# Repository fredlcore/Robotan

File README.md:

# Robotan
Die deutsche Version gibt es <A HREF="README_de.md">hier</A>.  

WiFi access to Zucchetti-based lawnmower robots (Ambrogio, Stiga, Herkules etc.)  
See a list of (partly still assumed) compatible robots <A HREF="Supported Models.md">here</A>.  
Some boards left over from a collective order are still available. Contact robotan (ät) code-it.de if you are interested (German or English).

<H2><A HREF="LICENSE.md">License</A></H2>
<H2><A HREF="Assembly Instructions.md">Building the Robotan board</A></H2>
<H2><A HREF="Installation.md">Installation</A></H2>
<H2><A HREF="Setup.md">Software Setup</A></H2>
<H2><A HREF="Configuration.md">Configuration</A></H2>
<H2><A HREF="Troubleshooting.md">Troubleshooting</A></H2>
<H2><A HREF="FAQ.md">Frequently Asked Questions (FAQ)</A></H2>

<B>Some screenshots:</B>  

<B>Web-based remote control:</B>

<IMG WIDTH=50% SRC="./img/web-based%20remote%20control.jpg">

<B>Web interface with configuration and status information:</B>

<IMG SRC="./img/web%20interface%20status%20configuration.jpg">

<B>General settings (incl. GPS):</B>

<IMG SRC="./img/Configurations.png">  

<B>Screencapture of realtime robot movements (new position polled every 10 seconds):</B>  
  
https://user-images.githubusercontent.com/24660955/123637079-e1455280-d81d-11eb-9b20-2d750a1a620e.mp4

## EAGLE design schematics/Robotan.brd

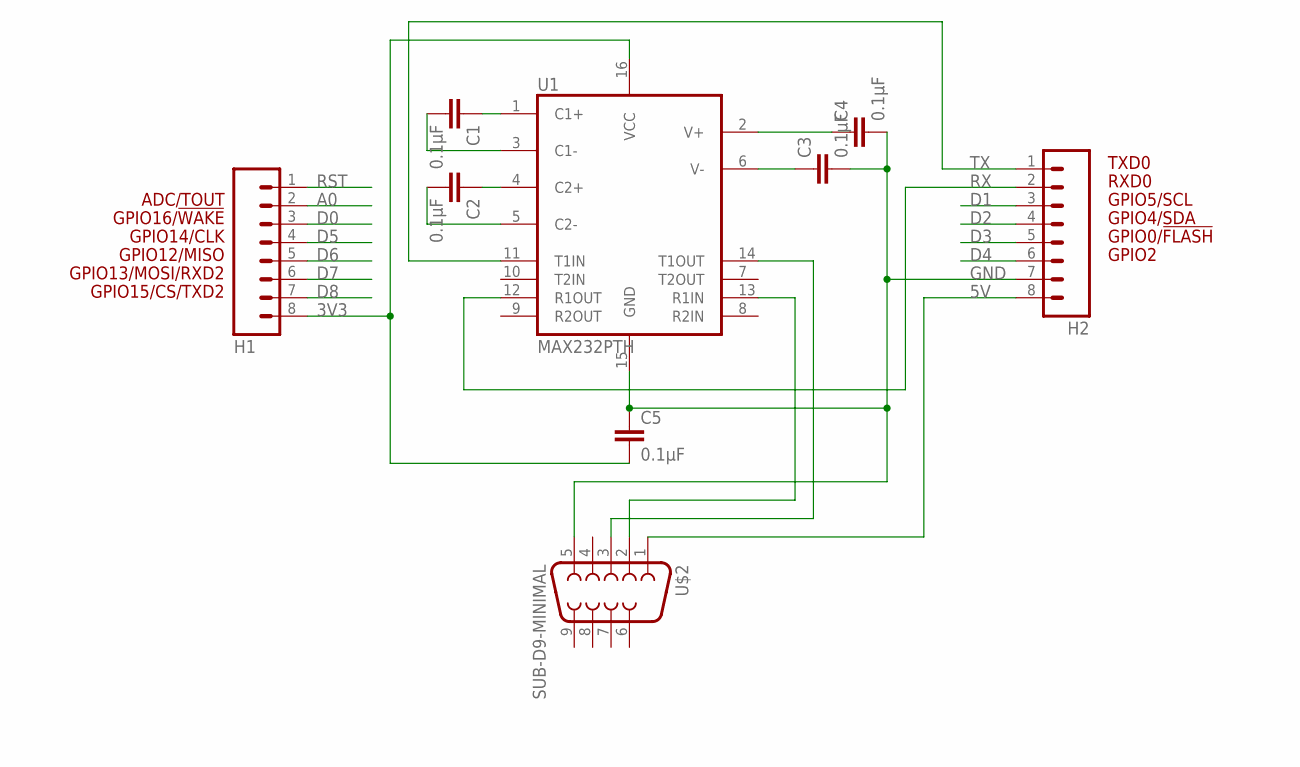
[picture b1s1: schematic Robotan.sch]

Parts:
C1, C2, C3, C4, C5: 0.1µF; CAP-PTH-SMALL-KIT
H1, H2: M08; 1X08
U1: MAX232PTH; DIL16
U$2: SUB-D9-MINIMAL

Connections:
3V3: C5.2, H1.8, U1.16 (VCC)
5V: H2.8, U$2.1
A0: H1.2
C1+: C1.1, U1.1 (C1+)
C1-: C1.2, U1.3 (C1-)
C2+: C2.1, U1.4 (C2+)
C2-: C2.2, U1.5 (C2-)
D0: H1.3
D1: H2.3
D2: H2.4
D3: H2.5
D4: H2.6
D5: H1.4
D6: H1.5
D7: H1.6
D8: H1.7
GND: C3.2, C4.2, C5.1, H2.7, U1.15 (GND), U$2.5
RS232_RX: U1.14 (T1OUT), U$2.3
RS232_TX: U1.13 (R1IN), U$2.2
RST: H1.1
RX: H2.2, U1.12 (R1OUT)
TX: H2.1, U1.11 (T1IN)
V+: C4.1, U1.2 (V+)
V-: C3.1, U1.6 (V-)

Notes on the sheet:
GPIO2
GPIO0/!FLASH
GPIO12/MISO
GPIO4/SDA
GPIO5/SCL
RXD0
TXD0
GPIO13/MOSI/RXD2
GPIO14/CLK
GPIO15/CS/TXD2
GPIO16/!WAKE
ADC/TOUT

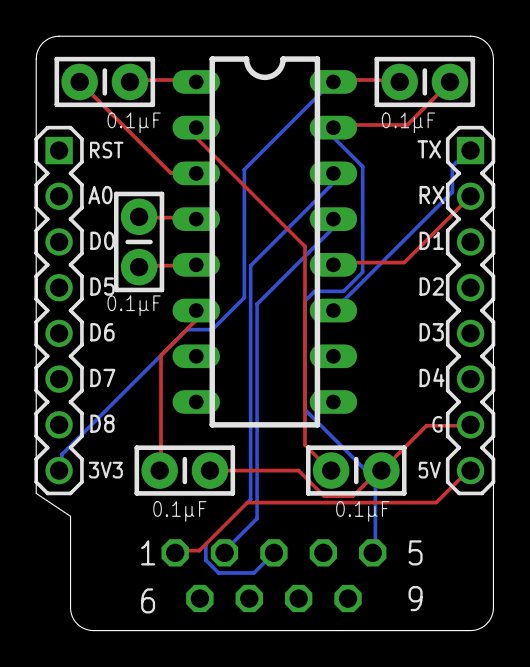
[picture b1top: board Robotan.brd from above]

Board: 2 copper layers, 25.4 x 33.0 mm, 9 parts (0 on the bottom side), 13 nets.

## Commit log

2017-11-08 Create test
2017-11-11 Bugfixes in board layout
2017-11-11 New Screenshots
2017-12-06 Example PHP script for sending notification via e-mail
2017-12-06 Initial list
2017-12-07 Installation sketch to upload firmware via WiFi
2017-12-07 Robotan firmware
2017-12-08 Added instruction images
2017-12-08 Sorted images
2017-12-08 Added arrows
2017-12-08 Arduino Settings
2017-12-08 Create Assembly Instructions
2017-12-08 Rename Assembly Instructions to Assembly Instructions.md
2017-12-08 Moved file
2017-12-12 German translations added
2017-12-12 German translations
2017-12-14 Updated supported models
2017-12-14 Updated license
2017-12-14 Added installation details
2017-12-15 Added authentification information
2018-01-02 New screenshot from Arduino IDE with ESP core 2.4.0
2018-03-01 Added instructions for additional capacitator
2018-03-01 Various bugfixes, enabled writing parameters
2018-03-08 Initial version of FHEM module
2018-03-08 Various bugfixes and smaller improvements
2018-03-09 Bugfixes
2018-03-17 IMPORTANT BUGFIX - please all update to this version if you cannot access your robot via WLAN (especially L85 and compativle)
2018-04-01 Added functionality, incl. write disable by default
2018-04-10 More models and functions
2018-04-10 Added various new commands, resulting in new command URLs. Update FHEM module as well if you use this version.
2018-04-11 Switched to table layout
2018-04-12 Added table entries
2018-05-17 Preliminary updates in FHEM module
2018-05-17 Sketch to (semi-)automatically configure HC-05/-06 etc. Bluetooth modules for use with Robotan
2018-06-09 Very important bugfix plus Bluetooth and joystick steering dunctionality
2018-06-09 Added Bluetooth module image
2018-06-09 Added model details for L75/L85 families
2018-06-09 Added Bluetooth module instructions
2018-07-04 Minor security updates
2018-08-08 Fixed collision between BT and GPS module polling
2018-08-12 Support for GPS logger implemented, major stability improvements
2018-08-12 Updated mobile screenshot
2018-08-12 Renamed from png to jpg
2018-08-13 Moved GPS module connection pins to 13 (D7, Robotan RX) and 15 (D8, Robotan TX, yet unsupported)
2018-08-16 Added configurable HTTP authentification and WiFi credentials
    Thanks to Oliver Weismantel for additions!
2018-08-16 Deleted RobotanSetup.ino.bin
2018-08-16 Added instructions for setting individual credentials
2018-08-17 Bugfix for Bluetooth-based firmware update
2018-08-23 Added GPS-based alerts for stuck robots as well as geo-fencing theft protection
2018-08-23 Added instructions for GPS module
2018-08-23 Added GPS configuration instructions
2018-08-23 Added configuration screenshot
2018-08-28 Screencapture of realtime robot movements
2018-08-28 Added Google satellite map with realtime robot position
2018-08-28 Added link to screencapture video
2018-08-28 Fixed screencap filename
2018-08-28 Fixed screencap video link
2018-08-28 Shortened video
2018-08-28 Fixed video duration
2018-08-28 Updated parts list
2018-08-28 Added buzzer instructions
2018-08-28 Added buzzer alarm plus important bugfix which prevented saving of configuration
2018-09-02 Greatly improved stability when using GPS module
2018-09-06 Added GPS image
2018-09-17 Updated instructions
2018-10-08 Add FHEM set commands
    Add FHEM set commands:
    set <device> Start_Time_2
    set <device> End_Time_2
2018-11-26 Further instructions added
2018-11-26 Various bugfixes
2018-12-02 Bugfix to prevent crash
2019-03-13 Removed due to commercial abuse
2019-03-18 Moved files to separate directories
2019-03-18 Bugfix
2019-03-18 Moved to separate directories
2019-04-23 Updated curl firmware update instructions
2019-04-23 Added URL command /gpio?x=y to set GPIO no. x to value y.
2019-04-30 Important update due to new memory layout with firmwares 41000 and above.
2019-05-01 Updated settings screenhot
2019-05-01 Notify URL now supports https, however no certificate checking is conducted!
2019-05-02 Added new "Go" command in Status menu
2019-05-03 Bugfix for empty configuration page
2019-05-05 Clear complete EEPROM memory for future extensions
2019-05-06 Added note that https calls for notifications are now possible
2019-05-06 Added instructions for directly accessing GPIO pins of the Wemos
2019-05-09 Updated capacitator value
2019-05-10 GPS borders on live map, 20 new stats, improved stability
2019-05-12 Bugfix for GPS fencing checkbox
2019-05-20 Cleanup
2019-05-20 Added support for ADXL335 accelerometer; important bugfixes
2019-05-20 Bugfix for GPS stuck detection
2019-05-23 Added instructions for ADXL335 acceleration sensor
2019-05-23 Added instructions for ADXL335 sensor
2019-06-01 Added info for AM4000 mainboard incompatibility!
2019-06-02 Spelling corrections
2019-06-02 Links to RobotanSetup.ino adjusted
2019-06-04 Support for ADXL335 and KY-003 sensors
2019-06-04 Updated instructions for ADXL335 and KY-003 sensors
2019-06-04 Added instructions for ADXL335 and KY-003 sensors
2019-06-05 Text formatting
2019-06-05 Links added
2019-06-09 Bugfix for acceleration sensor configuration
2019-06-12 New parameter "Docking Shift Distance" added; disabled several parameters for firmware versions < 41000 due to memory map changes by Zucchetti
2019-07-16 Added keyboard controls for steering: left/right arrow, P for pause, S for spiral, H/W for Home/Work
2019-10-02 Added parameters to JSON output
2019-10-10 Bugfix for resetting stuck counter
2019-10-12 Bugfix for stuck counter in JSON export
2019-10-15 Added Stiga 221 in compatibility list
2019-10-15 Added Stiga 221 to compatibility list
2019-10-15 Bugfix for false alarm in base
2019-10-26 Added Error Status in webinterface and JSON export
2020-04-25 Updated to new SoftwareSerial calls
2020-04-26 Clarified update procedure
2020-04-26 Bugfix for firmware update via Bluetooth
2020-04-30 Added notice for older stable version in case firmware update via Bluetooth fails
2020-05-10 New board layout
2020-05-10 Adjusted to new board layout
2020-05-10 Adjusted to newer board version
2020-05-10 No longer applicable
2020-05-18 Added workaround for unsupported "BLOCK1" error when robot is stuck for L30 MY17 and above
2020-06-02 Notify blocked L30 robot from MY17 onwards also when in transit or border mowing
2020-06-02 Highlight that only https notifications are possible
2020-06-07 Bugfix for notifying blocked L30 robot from MY17 onwards also when in transit or border mowing
2020-09-13 Added FHEM configuration instructions
2020-09-13 Added FHEM configuration options
2021-04-14 Updated https addresses
2021-06-16 Bluetooth auto-config fix
2021-06-28 Bugfix for displaying times and dates
2021-06-28 Added inline video of GPS function
2021-09-14 Update 98_Robotan.pm
    Small bugfixes
2024-10-21 Initial upload of EEPROM dumper

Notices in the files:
schematics/Robotan.brd:
Robotan - (C) 2017 Frederik Holst
parts and their libraries:
freetronics-original: Licensing: CC v3.0 Share-Alike You are welcome to use this library for commercial purposes.
SparkFun-Capacitors: Licensing: Creative Commons ShareAlike 4.0 International - https://creativecommons.org/licenses/by-sa/4.0
